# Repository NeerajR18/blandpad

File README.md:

# blandpad
Submission for Hack Club Blueprint 2026

blandpad is a basic 3x3 macropad with the XIAO RP2040 and KMK firmware.
It has buttons for media control, basic shortcuts and for opening applications.
The project was made to start learning about CAD and PCB Design.

# Features
- 3x3 Matrix layout with mechanical keys
- 3D printed case

# CAD
The case was designed in Autodesk Fusion
- Full Assembly

- Bottom

- Top

- Exploded View

# PCB

- Schematic

- PCB

# Firmware
The macropad uses KMK firmware. It has currently been programmed for media control and for functions such as screenshots.

# Bill Of Materials
## Bill of Materials

| Item Name | Qty. | Price (INR) | Link |
|----------|------|-------------|------|
| Seeed XIAO RP2040 | 1 | 618 | https://robu.in/product/seeed-studio-xiao-rp2040-v1-0/ |
| Through-hole 1N4148 Diodes | 9 | 3.14 | https://www.mouser.in/c/semiconductors/discrete-semiconductors/diodes-rectifiers/?mounting%20style=Through%20Hole&series=1N4148 |
| MX-Style Switches | 9 | 400 | https://www.amazon.in/Buildcon-Mechanical-Keyboard-Universal-Keyboards/dp/B0GCCQLQBV |
| DSA Keycaps | 9 | 541 | https://www.digikey.in/en/products/detail/adafruit-industries-llc/4998/14552195 |
| M3x16mm Screws | 9 | 235 | https://robu.in/product/easymech-ht-socket-button-head-cap-allen-bolt-m3-x-16-25-pcs/ |
| M3x4mm Heatset Inserts | 9 | 89 | https://robu.in/product/m3-x-4-mm-brass-heat-set-knurl-threaded-round-insert-nut-25-pcs/ |

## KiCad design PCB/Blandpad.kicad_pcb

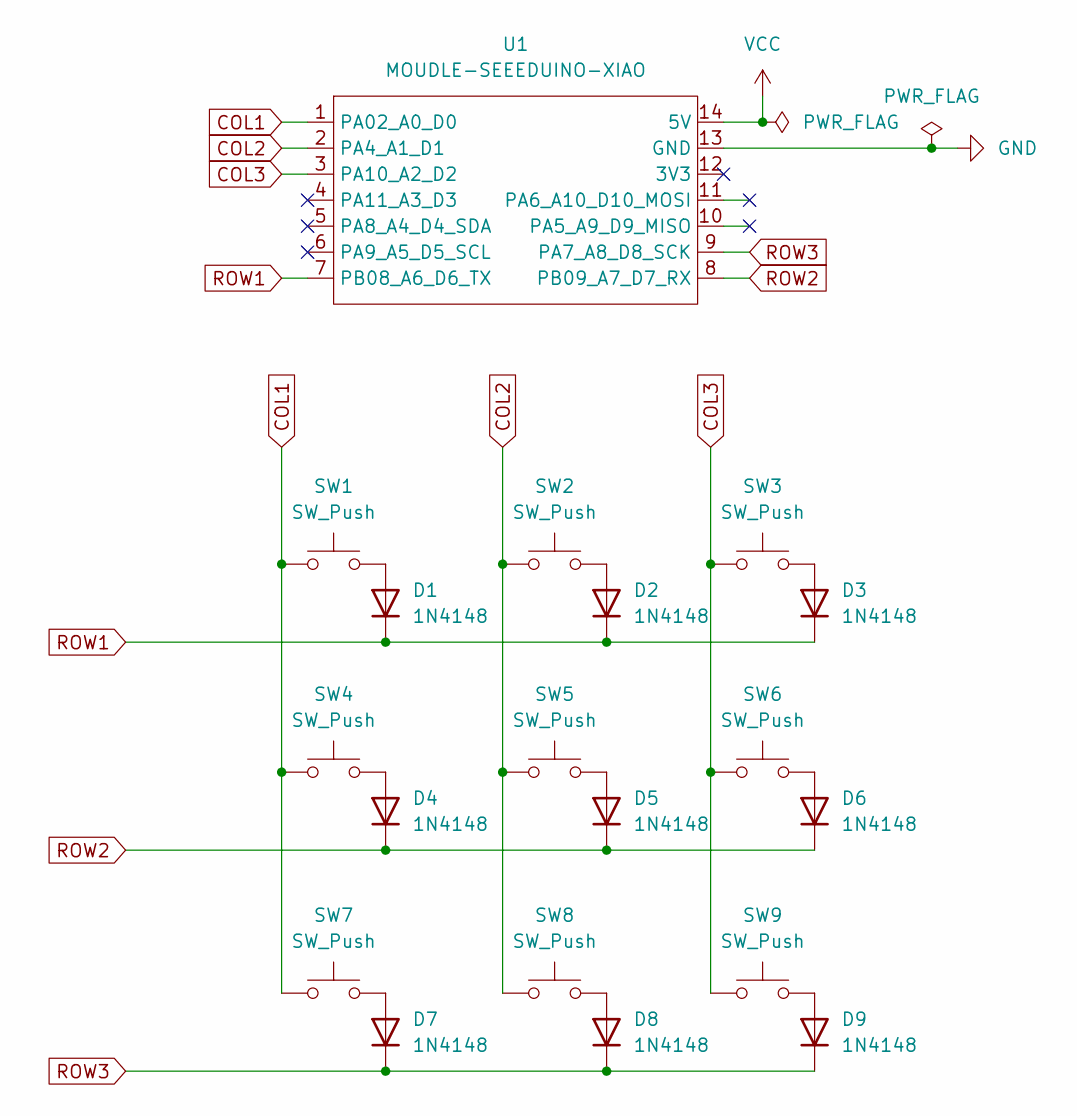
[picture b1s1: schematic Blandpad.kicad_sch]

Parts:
D1, D2, D3, D4, D5, D6, D7, D8, D9: 1N4148; D_DO-35_SOD27_P7.62mm_Horizontal
SW1, SW2, SW3, SW4, SW5, SW6, SW7, SW8, SW9: SW_Push; SW_Cherry_MX_1.00u_PCB
U1: MOUDLE-SEEEDUINO-XIAO; XIAO-Generic-Hybrid-14P-2.54-21X17.8MM

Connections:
COL1: SW1.1, SW4.1, SW7.1, U1.1 (PA02_A0_D0)
COL2: SW2.1, SW5.1, SW8.1, U1.2 (PA4_A1_D1)
COL3: SW3.1, SW6.1, SW9.1, U1.3 (PA10_A2_D2)
GND: U1.13 (GND)
unnamed: D1.2 (A), SW1.2
unnamed: D2.2 (A), SW2.2
unnamed: D3.2 (A), SW3.2
unnamed: D4.2 (A), SW4.2
unnamed: D5.2 (A), SW5.2
unnamed: D6.2 (A), SW6.2
unnamed: D7.2 (A), SW7.2
unnamed: D8.2 (A), SW8.2
unnamed: D9.2 (A), SW9.2
ROW1: D1.1 (K), D2.1 (K), D3.1 (K), U1.7 (PB08_A6_D6_TX)
ROW2: D4.1 (K), D5.1 (K), D6.1 (K), U1.8 (PB09_A7_D7_RX)
ROW3: D7.1 (K), D8.1 (K), D9.1 (K), U1.9 (PA7_A8_D8_SCK)
VCC: U1.14 (5V)

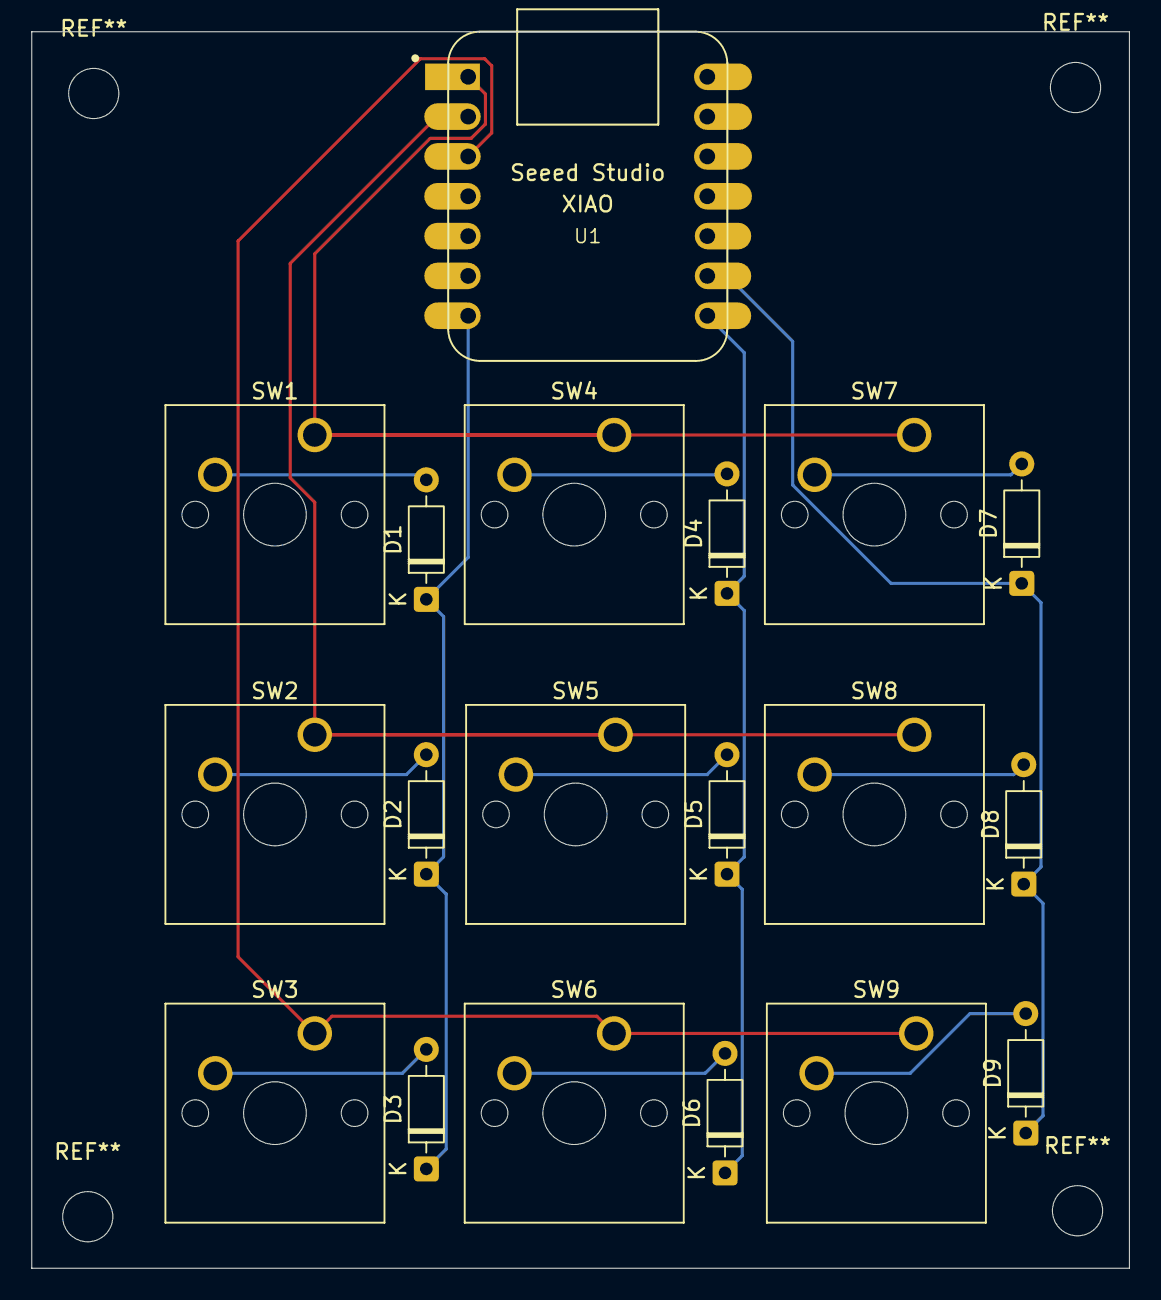
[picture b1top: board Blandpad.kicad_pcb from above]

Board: 2 copper layers, 70.0 x 78.9 mm, 19 parts (0 on the bottom side), 15 nets.

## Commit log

2026-03-23 final submission commit
    committed all required files together
2026-03-23 minor commit
2026-03-26 Corrections
    Added CAD models
2026-03-26 updated BOM
2026-03-27 Updated 3D Models
    Added step files
2026-03-29 Updated CAD files
2026-03-29 Updated images for CAD
    Updated images for CAD assembly views in README.
2026-05-27 Updated CAD images
